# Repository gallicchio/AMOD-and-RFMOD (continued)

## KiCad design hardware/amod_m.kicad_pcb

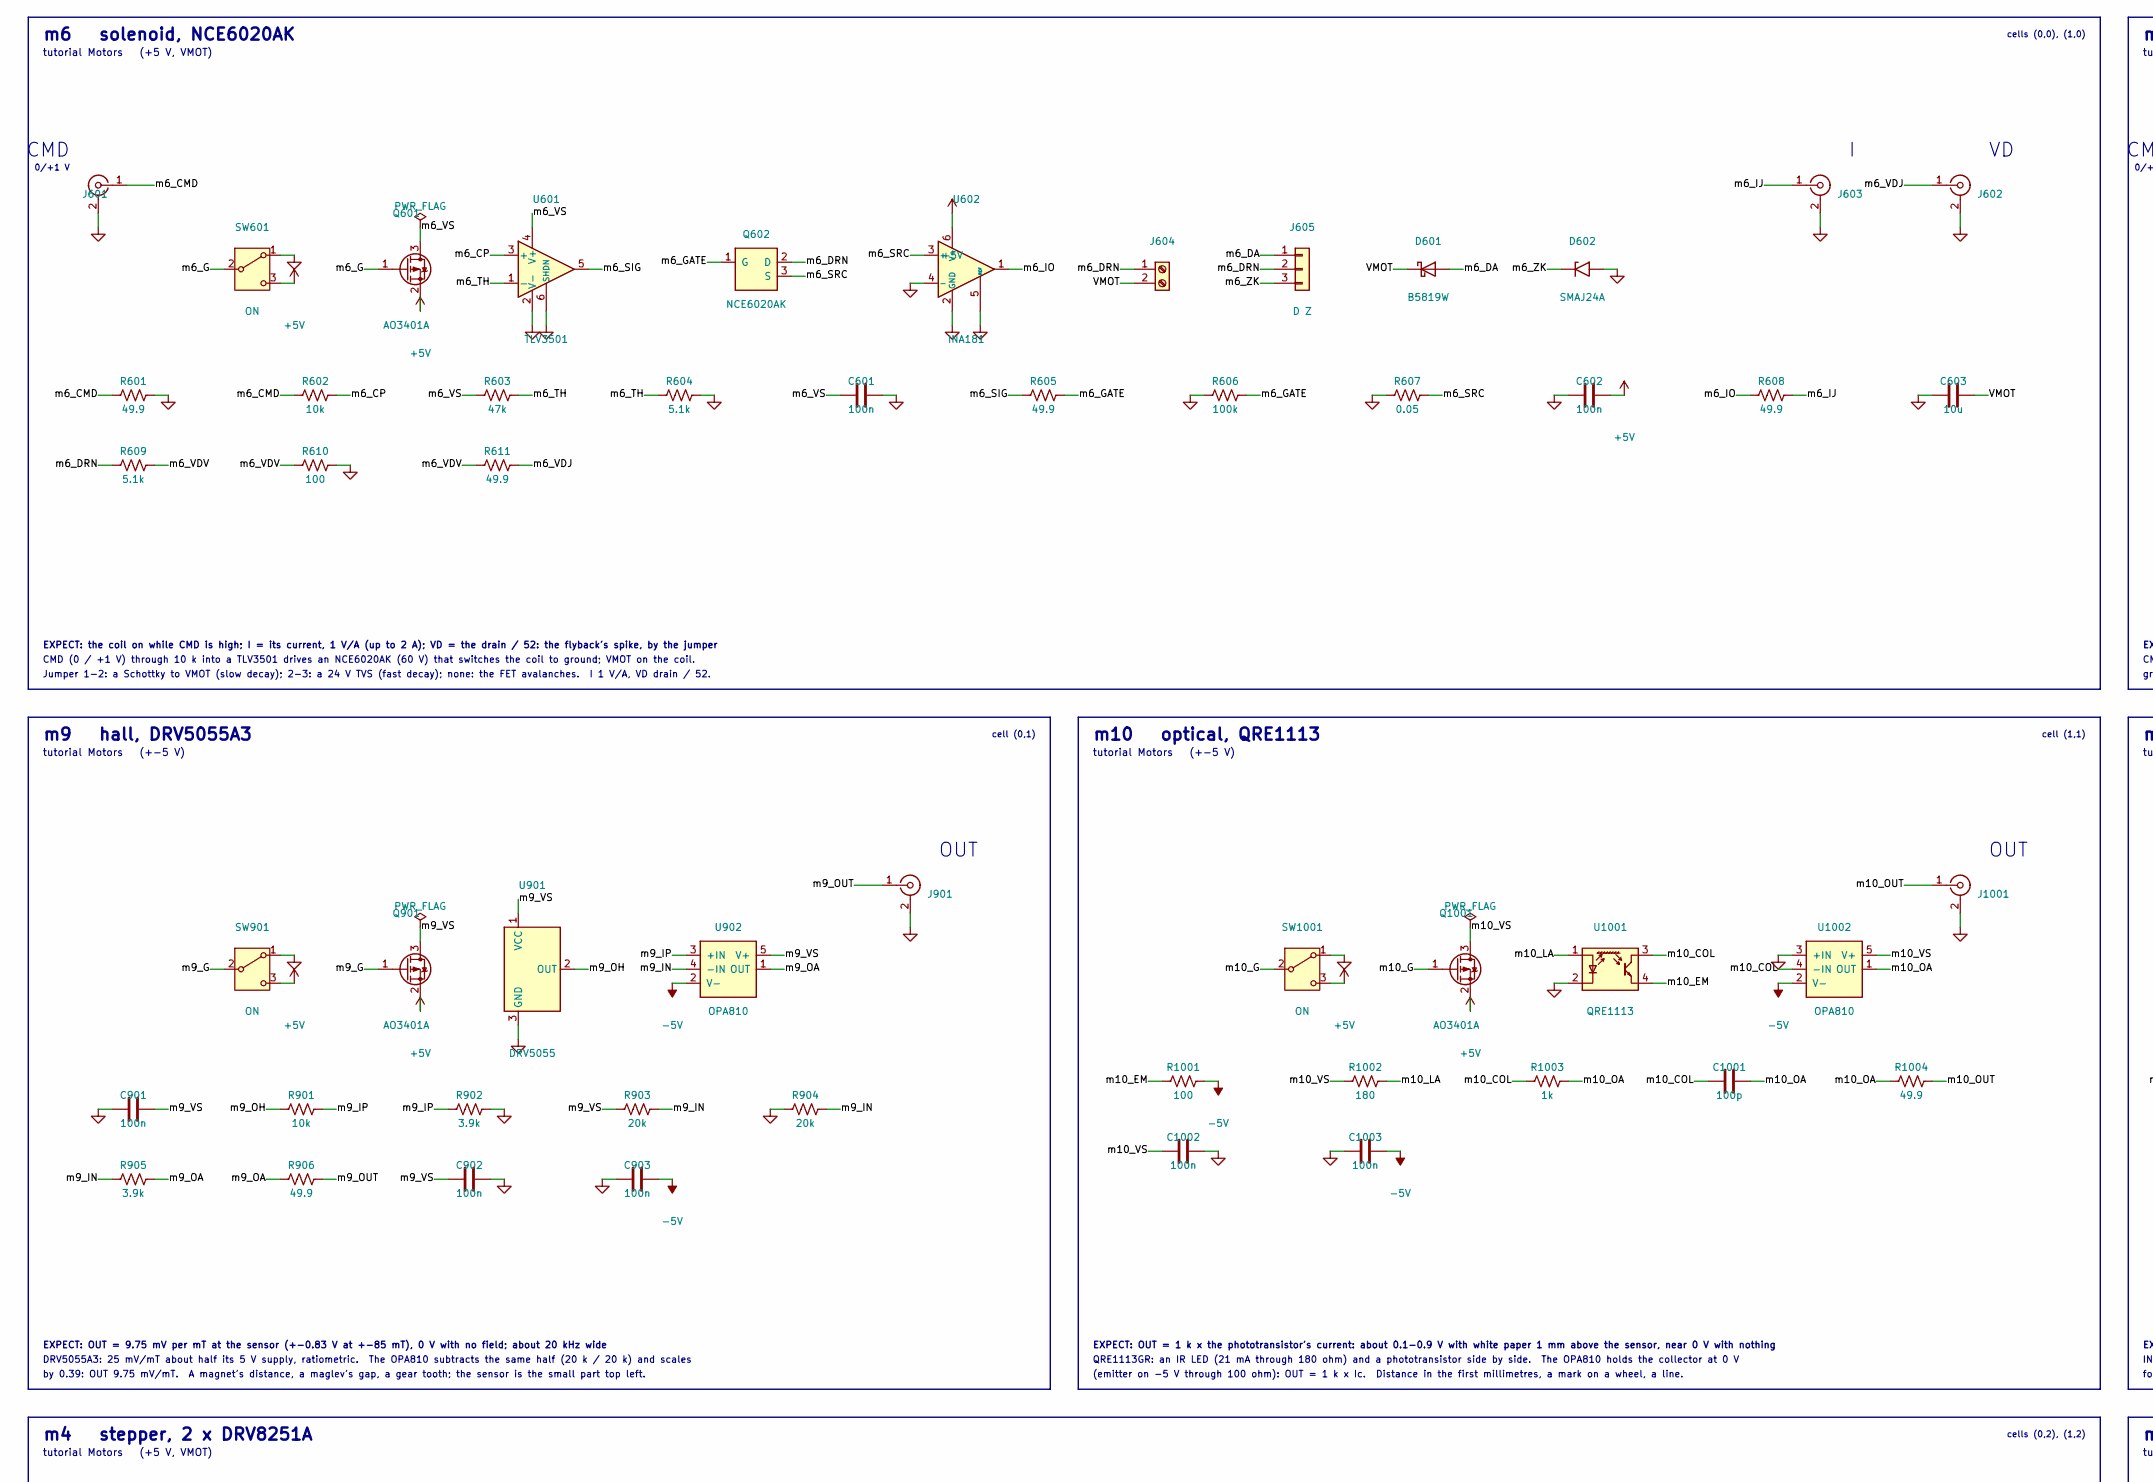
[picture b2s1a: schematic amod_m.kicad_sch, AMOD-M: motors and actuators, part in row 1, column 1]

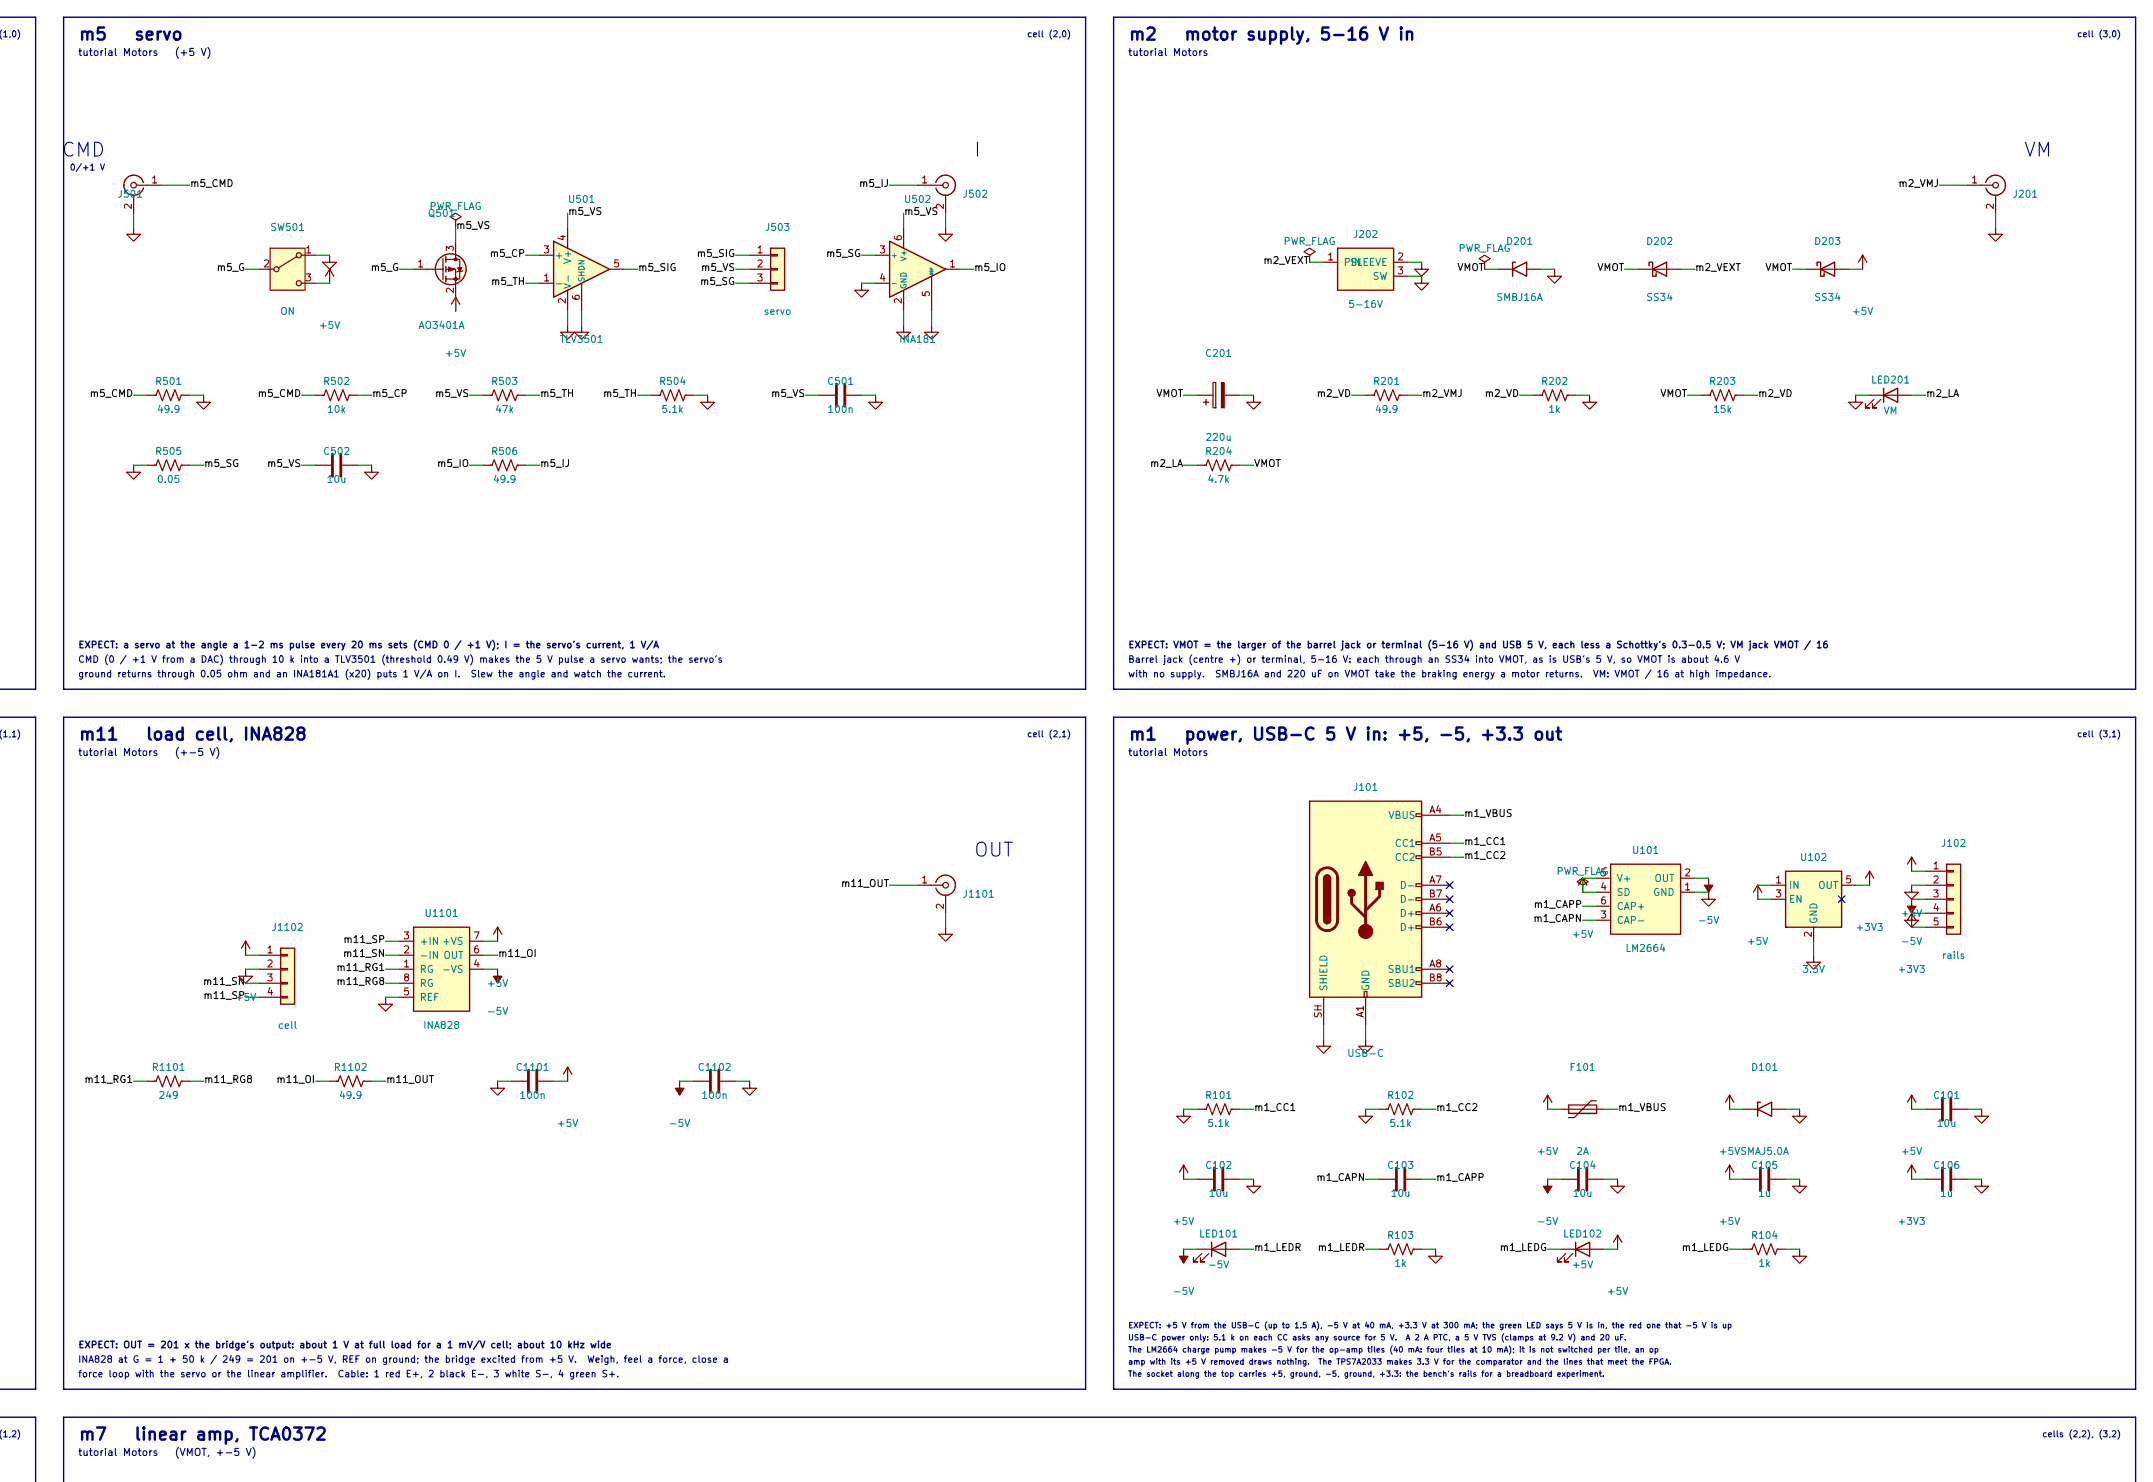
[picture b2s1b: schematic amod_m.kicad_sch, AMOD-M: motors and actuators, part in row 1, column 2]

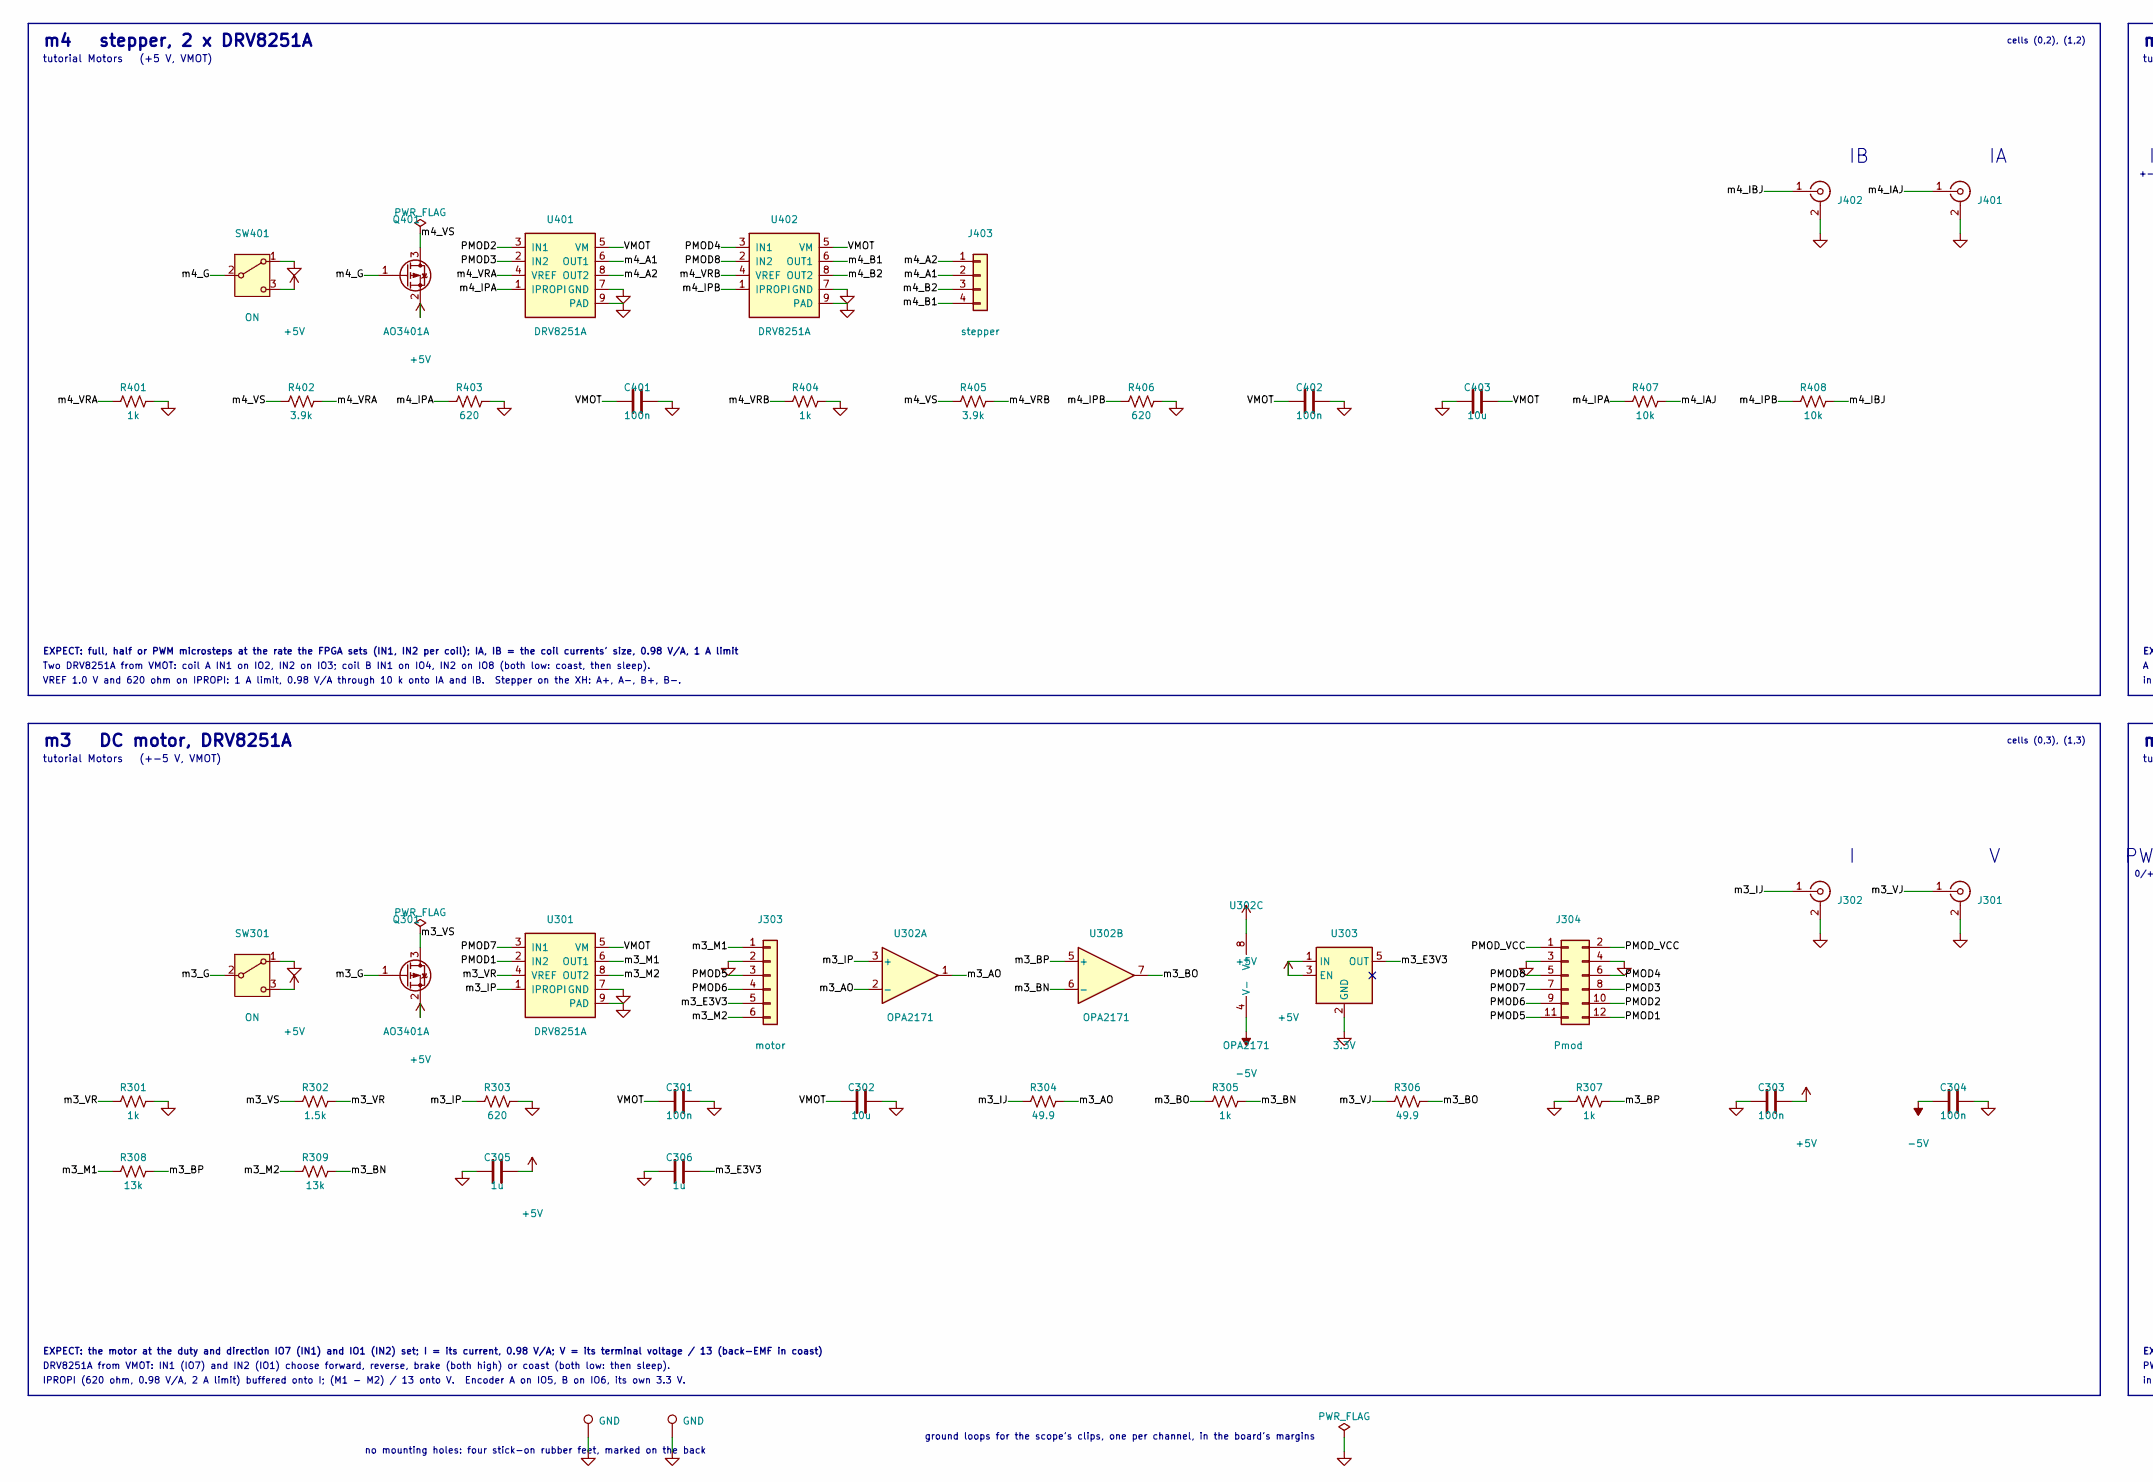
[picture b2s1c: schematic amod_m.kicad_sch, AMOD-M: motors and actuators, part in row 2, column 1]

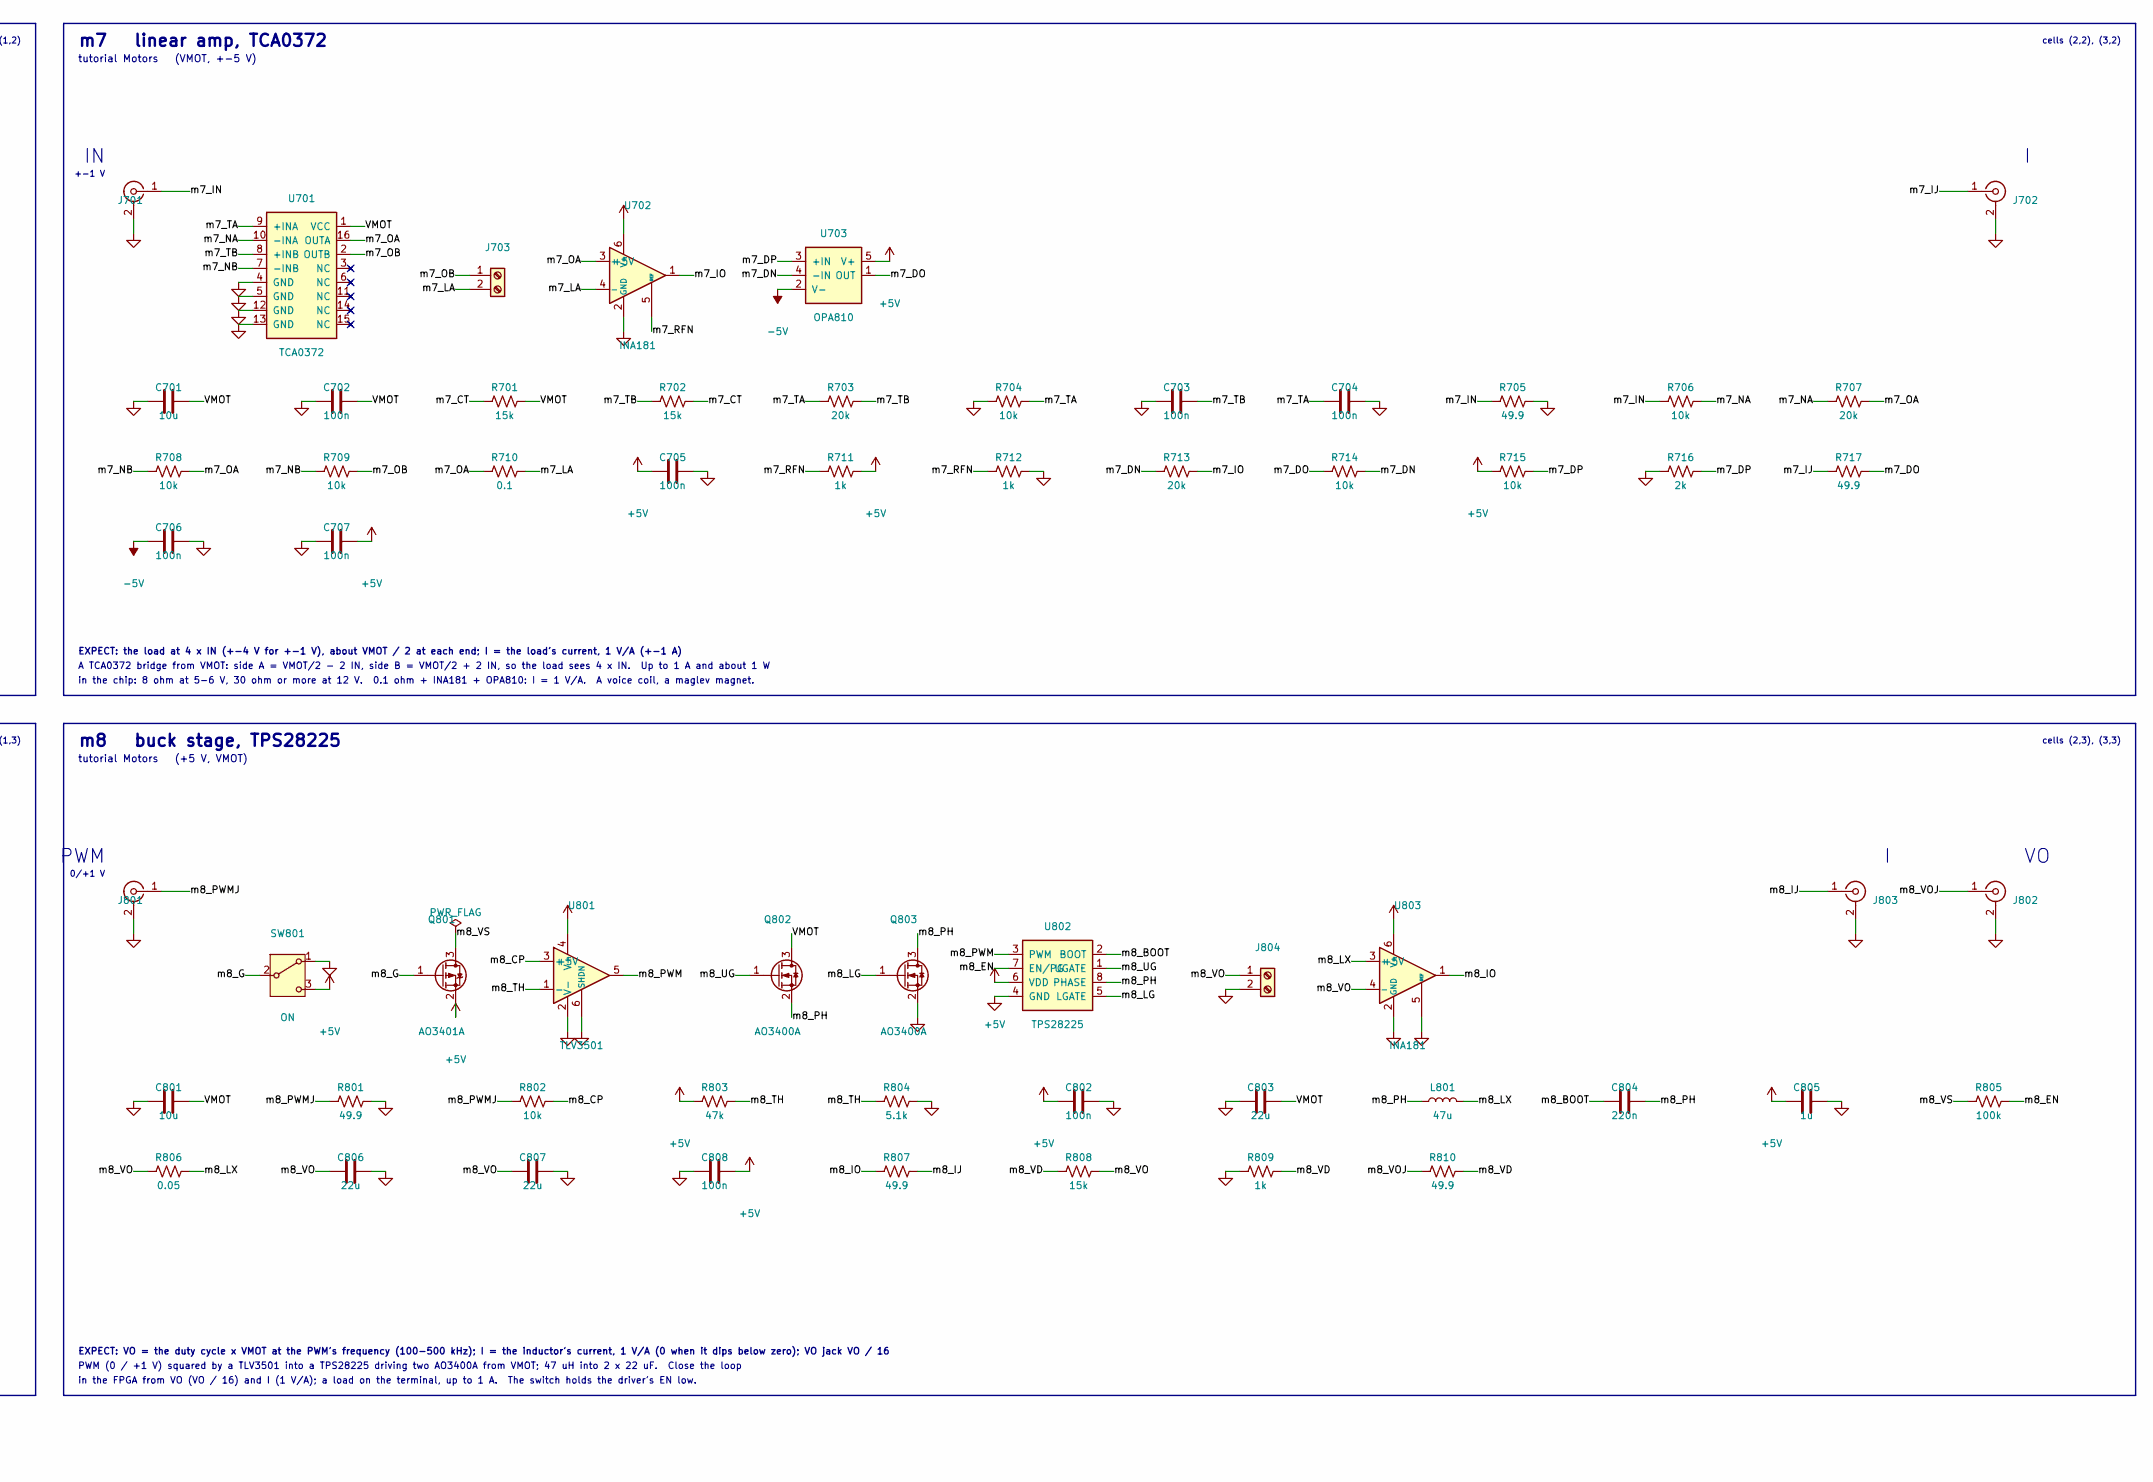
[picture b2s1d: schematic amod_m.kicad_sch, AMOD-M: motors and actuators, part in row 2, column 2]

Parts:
C101, C102, C103, C104, C302, C403, C502, C603, C701, C801: 10u; C_0805_2012Metric; MPN CL21A106KAYNNNE; LCSC C15850
C105, C106: 1u; C_0805_2012Metric; MPN CL21B105KBFNNNE; LCSC C28323
C201: 220u; CP_Elec_6.3x7.7; MPN XT220UF25V90RV0075; LCSC C2992606
C301, C303, C304, C401, C402, C501, C601, C602, C702, C703, C704, C705, C706, C707, C802, C808, C901, C902, C903, C1002, C1003, C1101, C1102: 100n; C_0402_1005Metric; MPN CL05B104KO5NNNC; LCSC C1525
C305, C306, C805: 1u; C_0603_1608Metric; MPN CL10A105KB8NNNC; LCSC C15849
C803, C806, C807: 22u; C_1206_3216Metric; MPN CL31A226KAHNNNE; LCSC C12891
C804: 220n; C_0402_1005Metric; MPN CL05B224KO5NNNC; LCSC C16772
C1001: 100p; C_0402_1005Metric; MPN 0402CG101J500NT; LCSC C1546
D101: SMAJ5.0A; D_SMA; MPN SMAJ5.0A; LCSC C78401
D201: SMBJ16A; D_SMB; MPN SMBJ16A; LCSC C353386
D202, D203: SS34; D_SMA; MPN SS34; LCSC C8678
D601: B5819W; D_SOD-123; MPN B5819W; LCSC C64885
D602: SMAJ24A; D_SMA; MPN SMAJ24A; LCSC C113962
F101: 2A; Fuse_1812_4532Metric; MPN MF-MSMF200-2; LCSC C210837
J101: USB-C; USB_C_Receptacle_HRO_TYPE-C-31-M-12; MPN TYPE-C-31-M-12; LCSC C165948
J102: rails; PinSocket_1x05_P2.54mm_Vertical; MPN PZ254-1-05-Z-8.5; LCSC C2894928
J201, J301, J302, J401, J402, J501, J502, J601, J602, J603, J701, J702, J801, J802, J803, J901, J1001, J1101: SMA; SMA_BWSMA-KE-Z001_Vertical; MPN BWSMA-KE-Z001; LCSC C496549
J202: 5-16V; BarrelJack_DC-005-5A_Horizontal; MPN DC-005-5A-2.0; LCSC C381116
J303: motor; JST_PH_B6B-PH-K_1x06_P2.00mm_Vertical; MPN B6B-PH-K-S(LF)(SN); LCSC C131342
J304: Pmod; PinHeader_2x06_P2.54mm_Horizontal_PZ254R-12-12P; MPN PZ254R-12-12P; LCSC C492434
J403: stepper; JST_XH_B4B-XH-A_1x04_P2.50mm_Vertical; MPN B4B-XH-A(LF)(SN); LCSC C144395
J503: servo; PinHeader_1x03_P2.54mm_Vertical; MPN PZ254V-11-03P; LCSC C2937625
J604: coil; TerminalBlock_KF301_1x02_P5.00mm; MPN KF301-5.0-2P; LCSC C474881
J605: D Z; PinHeader_1x03_P2.54mm_Vertical; MPN PZ254V-11-03P; LCSC C2937625
J703: load; TerminalBlock_KF301_1x02_P5.00mm; MPN KF301-5.0-2P; LCSC C474881
J804: out; TerminalBlock_KF301_1x02_P5.00mm; MPN KF301-5.0-2P; LCSC C474881
J1102: cell; JST_XH_B4B-XH-A_1x04_P2.50mm_Vertical; MPN B4B-XH-A(LF)(SN); LCSC C144395
L801: 47u; L_6x6_SWPA6045; MPN SWPA6045S470MT; LCSC C36414
LED101: -5V; LED_0805_2012Metric_Kbar; MPN NCD0805R1; LCSC C84256
LED102: +5V; LED_0805_2012Metric_Kbar; MPN KT-0805G; LCSC C2297
LED201: VM; LED_0805_2012Metric_Kbar; MPN KT-0805G; LCSC C2297
Q301, Q401, Q501, Q601, Q801, Q901, Q1001: AO3401A; SOT-23; MPN AO3401A; LCSC C15127
Q602: NCE6020AK; TO-252-2; MPN NCE6020AK; LCSC C108639
Q802, Q803: AO3400A; SOT-23; MPN AO3400A; LCSC C20917
R101, R102, R609: 5.1k; R_0805_2012Metric; MPN 0805W8F5101T5E; LCSC C27834
R103, R104: 1k; R_0805_2012Metric; MPN 0805W8F1001T5E; LCSC C17513
R201, R304, R306, R501, R506, R601, R605, R608, R611, R705, R717, R801, R807, R810, R906, R1004, R1102: 49.9; R_0402_1005Metric; MPN CRCW040249R9FKEDHP; LCSC C844112
R202, R301, R305, R307, R401, R404, R711, R712, R809, R1003: 1k; R_0402_1005Metric; MPN 0402WGF1001TCE; LCSC C11702
R203, R701, R702, R808: 15k; R_0402_1005Metric; MPN 0402WGF1502TCE; LCSC C25756
R204: 4.7k; R_0402_1005Metric; MPN 0402WGF4701TCE; LCSC C25900
R302: 1.5k; R_0402_1005Metric; MPN 0402WGF1501TCE; LCSC C25867
R303, R403, R406: 620; R_0402_1005Metric; MPN 0402WGF6200TCE; LCSC C4961
R308, R309: 13k; R_0402_1005Metric; MPN 0402WGF1302TCE; LCSC C25754
R402, R405, R902, R905: 3.9k; R_0402_1005Metric; MPN 0402WGF3901TCE; LCSC C51721
R407, R408, R502, R602, R704, R706, R708, R709, R714, R715, R802, R901: 10k; R_0402_1005Metric; MPN 0402WGF1002TCE; LCSC C25744
R503, R603, R803: 47k; R_0402_1005Metric; MPN 0402WGF4702TCE; LCSC C25792
R504, R604, R804: 5.1k; R_0402_1005Metric; MPN 0402WGF5101TCE; LCSC C25905
R505, R607, R806: 0.05; R_1206_3216Metric; MPN 1206W3F500MT5E; LCSC C127691
R606, R805: 100k; R_0402_1005Metric; MPN 0402WGF1003TCE; LCSC C25741
R610, R1001: 100; R_0402_1005Metric; MPN 0402WGF1000TCE; LCSC C25076
R703, R707, R713, R903, R904: 20k; R_0402_1005Metric; MPN 0402WGF2002TCE; LCSC C25765
R710: 0.1; R_1206_3216Metric; MPN 1206W4F100LT5E; LCSC C25334
R716: 2k; R_0402_1005Metric; MPN 0402WGF2001TCE; LCSC C4109
R1002: 180; R_0805_2012Metric; MPN 0805W8F1800T5E; LCSC C25270
R1101: 249; R_0402_1005Metric; MPN 0402WGF2490TCE; LCSC C25096
SW301, SW401, SW501, SW601, SW801, SW901, SW1001: ON; SW_SPDT_Shouhan_MSK12C02; MPN MSK12C02; LCSC C431540
TP9901, TP9902: GND; TestPoint_Loop_RH-5019; MPN RH-5019; LCSC C5199800
U101: LM2664; SOT-23-6; MPN LM2664M6X/NOPB; LCSC C108573
U102, U303: 3.3V; SOT-23-5; MPN TPS7A2033PDBVR; LCSC C2862740
U301, U401, U402: DRV8251A; HSOP-8-1EP_3.9x4.9mm_P1.27mm_EP2.41x3.1mm; MPN DRV8251ADDAR; LCSC C5218844
U302: OPA2171; SOIC-8_3.9x4.9mm_P1.27mm; MPN OPA2171AIDR; LCSC C40904
U501, U601, U801: TLV3501; SOT-23-6; MPN TLV3501AIDBVR; LCSC C193413
U502, U602, U702, U803: INA181; SOT-23-6; MPN INA181A1IDBVR; LCSC C2058943
U701: TCA0372; SOIC-16W_7.5x10.3mm_P1.27mm; MPN TCA0372DWR2G; LCSC C362060
U703, U902, U1002: OPA810; SOT-23-5; MPN OPA810IDBVR; LCSC C2833513
U802: TPS28225; SOIC-8_3.9x4.9mm_P1.27mm; MPN TPS28225DR; LCSC C52897
U901: DRV5055; SOT-23; MPN DRV5055A3QDBZR; LCSC C266128
U1001: QRE1113; OnSemi_CASE100CY; MPN QRE1113GR; LCSC C232862
U1101: INA828; SOIC-8_3.9x4.9mm_P1.27mm; MPN INA828IDR; LCSC C544342

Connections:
+3V3: C106.1, J102.5, U102.5 (OUT)
+5V: C101.1, C102.1, C105.1, C303.2, C305.2, C602.2, C705.1, C707.2, C802.1, C805.1, C808.2, C1101.2, D101.1 (A1), D203.2 (A), F101.1, J102.1, J1102.1, LED102.2 (A), Q301.2 (S), Q401.2 (S), Q501.2 (S), Q601.2 (S), Q801.2 (S), Q901.2 (S), Q1001.2 (S), R711.2, R715.1, R803.1, SW301.3 (C), SW401.3 (C), SW501.3 (C), SW601.3 (C), SW801.3 (C), SW901.3 (C), SW1001.3 (C), U101.4 (SD), U101.5 (V+), U102.1 (IN), U102.3 (EN), U302.8 (V+), U303.1 (IN), U303.3 (EN), U602.6 (V+), U702.6 (V+), U703.5 (V+), U801.4 (V+), U802.6 (VDD), U803.6 (V+), U1101.7 (+VS)
-5V: C104.1, C304.1, C706.1, C903.2, C1003.2, C1102.1, J102.3, LED101.1 (K), R1001.2, U101.2 (OUT), U302.4 (V-), U703.2 (V-), U902.2 (V-), U1002.2 (V-), U1101.4 (-VS)
/PMOD1: J304.12, U301.2 (IN2)
/PMOD2: J304.10, U401.3 (IN1)
/PMOD3: J304.8, U401.2 (IN2)
/PMOD4: J304.6, U402.3 (IN1)
/PMOD5: J303.3, J304.11
/PMOD6: J303.4, J304.9
/PMOD7: J304.7, U301.3 (IN1)
/PMOD8: J304.5, U402.2 (IN2)
/PMOD_VCC: J304.1, J304.2
/VMOT: C201.1, C301.1, C302.1, C401.1, C402.1, C403.2, C603.2, C701.2, C702.2, C801.2, C803.2, D201.1 (A1), D202.1 (K), D203.1 (K), D601.1 (K), J604.2, Q802.3 (D), R203.1, R204.2, R701.2, U301.5 (VM), U401.5 (VM), U402.5 (VM), U701.1 (VCC)
/m1_CAPN: C103.1, U101.3 (CAP-)
/m1_CAPP: C103.2, U101.6 (CAP+)
/m1_CC1: J101.A5 (CC1), R101.2
/m1_CC2: J101.B5 (CC2), R102.2
/m1_LEDG: LED102.1 (K), R104.1
/m1_LEDR: LED101.2 (A), R103.1
/m1_VBUS: F101.2, J101.A4 (VBUS), J101.A9 (VBUS), J101.B4 (VBUS), J101.B9 (VBUS)
/m2_LA: LED201.2 (A), R204.1
/m2_VD: R201.1, R202.1, R203.2
/m2_VEXT: D202.2 (A), J202.1 (PIN)
/m2_VMJ: J201.1 (In), R201.2
/m3_AO: R304.2, U302.1, U302.2 (-)
/m3_BN: R305.2, R309.2, U302.6 (-)
/m3_BO: R305.1, R306.2, U302.7
/m3_BP: R307.2, R308.2, U302.5 (+)
/m3_E3V3: C306.2, J303.5, U303.5 (OUT)
/m3_G: Q301.1 (G), SW301.2 (B)
/m3_IJ: J302.1 (In), R304.1
/m3_IP: R303.1, U301.1 (IPROPI), U302.3 (+)
/m3_M1: J303.1, R308.1, U301.6 (OUT1)
/m3_M2: J303.6, R309.1, U301.8 (OUT2)
/m3_VJ: J301.1 (In), R306.1
/m3_VR: R301.1, R302.2, U301.4 (VREF)
/m3_VS: Q301.3 (D), R302.1
/m4_A1: J403.2, U401.6 (OUT1)
/m4_A2: J403.1, U401.8 (OUT2)
/m4_B1: J403.4, U402.6 (OUT1)
/m4_B2: J403.3, U402.8 (OUT2)
/m4_G: Q401.1 (G), SW401.2 (B)
/m4_IAJ: J401.1 (In), R407.2
/m4_IBJ: J402.1 (In), R408.2
/m4_IPA: R403.1, R407.1, U401.1 (IPROPI)
/m4_IPB: R406.1, R408.1, U402.1 (IPROPI)
/m4_VRA: R401.1, R402.2, U401.4 (VREF)
/m4_VRB: R404.1, R405.2, U402.4 (VREF)
/m4_VS: Q401.3 (D), R402.1, R405.1
/m5_CMD: J501.1 (In), R501.1, R502.1
/m5_CP: R502.2, U501.3 (+)
/m5_G: Q501.1 (G), SW501.2 (B)
/m5_IJ: J502.1 (In), R506.2
/m5_IO: R506.1, U502.1
/m5_SG: J503.3, R505.2, U502.3 (+)
/m5_SIG: J503.1, U501.5
/m5_TH: R503.2, R504.1, U501.1 (-)
/m5_VS: C501.1, C502.1, J503.2, Q501.3 (D), R503.1, U501.4 (V+), U502.6 (V+)
/m6_CMD: J601.1 (In), R601.1, R602.1
/m6_CP: R602.2, U601.3 (+)
/m6_DA: D601.2 (A), J605.1
/m6_DRN: J604.1, J605.2, Q602.2 (D), R609.1
/m6_G: Q601.1 (G), SW601.2 (B)
/m6_GATE: Q602.1 (G), R605.2, R606.2
/m6_IJ: J603.1 (In), R608.2
/m6_IO: R608.1, U602.1
/m6_SIG: R605.1, U601.5
/m6_SRC: Q602.3 (S), R607.2, U602.3 (+)
/m6_TH: R603.2, R604.1, U601.1 (-)
/m6_VDJ: J602.1 (In), R611.2
/m6_VDV: R609.2, R610.1, R611.1
/m6_VS: C601.1, Q601.3 (D), R603.1, U601.4 (V+)
/m6_ZK: D602.1 (A1), J605.3
/m7_CT: R701.1, R702.2
/m7_DN: R713.1, R714.2, U703.4 (-IN)
/m7_DO: R714.1, R717.2, U703.1 (OUT)
/m7_DP: R715.2, R716.2, U703.3 (+IN)
/m7_IJ: J702.1 (In), R717.1
/m7_IN: J701.1 (In), R705.1, R706.1
/m7_IO: R713.2, U702.1
/m7_LA: J703.2, R710.2, U702.4 (-)
/m7_NA: R706.2, R707.1, U701.10 (-INA)
/m7_NB: R708.1, R709.1, U701.7 (-INB)
/m7_OA: R707.2, R708.2, R710.1, U701.16 (OUTA), U702.3 (+)
/m7_OB: J703.1, R709.2, U701.2 (OUTB)
/m7_RFN: R711.1, R712.1, U702.5 (REF)
/m7_TA: C704.1, R703.1, R704.2, U701.9 (+INA)
/m7_TB: C703.2, R702.1, R703.2, U701.8 (+INB)
/m8_BOOT: C804.1, U802.2 (BOOT)
/m8_CP: R802.2, U801.3 (+)
/m8_EN: R805.2, U802.7 (EN/PG)
/m8_G: Q801.1 (G), SW801.2 (B)
/m8_IJ: J803.1 (In), R807.2
/m8_IO: R807.1, U803.1
/m8_LG: Q803.1 (G), U802.5 (LGATE)
/m8_LX: L801.2, R806.2, U803.3 (+)
/m8_PH: C804.2, L801.1, Q802.2 (S), Q803.3 (D), U802.8 (PHASE)
/m8_PWM: U801.5, U802.3 (PWM)
/m8_PWMJ: J801.1 (In), R801.1, R802.1
/m8_TH: R803.2, R804.1, U801.1 (-)
/m8_UG: Q802.1 (G), U802.1 (UGATE)
/m8_VD: R808.1, R809.2, R810.2
/m8_VO: C806.1, C807.1, J804.1, R806.1, R808.2, U803.4 (-)
/m8_VOJ: J802.1 (In), R810.1
/m8_VS: Q801.3 (D), R805.1
/m9_G: Q901.1 (G), SW901.2 (B)
/m9_IN: R903.2, R904.2, R905.1, U902.4 (-IN)
/m9_IP: R901.2, R902.1, U902.3 (+IN)
/m9_OA: R905.2, R906.1, U902.1 (OUT)
/m9_OH: R901.1, U901.2 (OUT)
/m9_OUT: J901.1 (In), R906.2
/m9_VS: C901.2, C902.1, Q901.3 (D), R903.1, U901.1 (VCC), U902.5 (V+)
/m10_COL: C1001.1, R1003.1, U1001.3, U1002.4 (-IN)
/m10_EM: R1001.1, U1001.4
/m10_G: Q1001.1 (G), SW1001.2 (B)
/m10_LA: R1002.2, U1001.1 (A)
/m10_OA: C1001.2, R1003.2, R1004.1, U1002.1 (OUT)
/m10_OUT: J1001.1 (In), R1004.2
/m10_VS: C1002.1, Q1001.3 (D), R1002.1, U1002.5 (V+)
/m11_OI: R1102.1, U1101.6 (OUT)
/m11_OUT: J1101.1 (In), R1102.2
/m11_RG1: R1101.1, U1101.1 (RG)
/m11_RG8: R1101.2, U1101.8 (RG)
/m11_SN: J1102.3, U1101.2 (-IN)
/m11_SP: J1102.4, U1101.3 (+IN)
GND: C101.2, C102.2, C104.2, C105.2, C106.2, C201.2, C301.2, C302.2, C303.1, C304.2, C305.1, C306.1, C401.2, C402.2, C403.1, C501.2, C502.2, C601.2, C602.1, C603.1, C701.1, C702.1, C703.1, C704.2, C705.2, C706.2, C707.1, C801.1, C802.2, C803.1, C805.2, C806.2, C807.2, C808.1, C901.1, C902.2, C903.1, C1002.2, C1003.1, C1101.1, C1102.2, D101.2 (A2), D201.2 (A2), D602.2 (A2), J101.A1 (GND), J101.A12 (GND), J101.B1 (GND), J101.B12 (GND), J101.SH (SHIELD), J102.2, J102.4, J201.2 (Ext), J202.2 (SLEEVE), J202.3 (SW), J301.2 (Ext), J302.2 (Ext), J303.2, J304.3, J304.4, J401.2 (Ext), J402.2 (Ext), J501.2 (Ext), J502.2 (Ext), J601.2 (Ext), J602.2 (Ext), J603.2 (Ext), J701.2 (Ext), J702.2 (Ext), J801.2 (Ext), J802.2 (Ext), J803.2 (Ext), J804.2, J901.2 (Ext), J1001.2 (Ext), J1101.2 (Ext), J1102.2, LED201.1 (K), Q803.2 (S), R101.1, R102.1, R103.2, R104.2, R202.2, R301.2, R303.2, R307.1, R401.2, R403.2, R404.2, R406.2, R501.2, R504.2, R505.1, R601.2, R604.2, R606.1, R607.1, R610.2, R704.1, R705.2, R712.2, R716.1, R801.2, R804.2, R809.1, R902.2, R904.1, SW301.1 (A), SW401.1 (A), SW501.1 (A), SW601.1 (A), SW801.1 (A), SW901.1 (A), SW1001.1 (A), TP9901.1, TP9902.1, U101.1 (GND), U102.2 (GND), U301.7 (GND), U301.9 (PAD), U303.2 (GND), U401.7 (GND), U401.9 (PAD), U402.7 (GND), U402.9 (PAD), U501.2 (V-), U501.6 (SHDN), U502.2 (GND), U502.4 (-), U502.5 (REF), U601.2 (V-), U601.6 (SHDN), U602.2 (GND), U602.4 (-), U602.5 (REF), U701.4 (GND), U701.5 (GND), U701.12 (GND), U701.13 (GND), U702.2 (GND), U801.2 (V-), U801.6 (SHDN), U802.4 (GND), U803.2 (GND), U803.5 (REF), U901.3 (GND), U1001.2 (K), U1002.3 (+IN), U1101.5 (REF)

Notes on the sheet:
CMD
OUT
cells (2,2), (3,2)
cell (2,1)
Two DRV8251A from VMOT: coil A IN1 on IO2, IN2 on IO3; coil B IN1 on IO4, IN2 on IO8 (both low: coast, then sleep).
DRV8251A from VMOT: IN1 (IO7) and IN2 (IO1) choose forward, reverse, brake (both high) or coast (both low: then sleep).
cell (2,0)
m4 stepper, 2 x DRV8251A
INA828 at G = 1 + 50 k / 249 = 201 on +-5 V, REF on ground; the bridge excited from +5 V. Weigh, feel a force, close a
USB-C power only: 5.1 k on each CC asks any source for 5 V. A 2 A PTC, a 5 V TVS (clamps at 9.2 V) and 20 uF.
EXPECT: the coil on while CMD is high; I = its current, 1 V/A (up to 2 A); VD = the drain / 52: the flyback's spike, by the jumper
EXPECT: VO = the duty cycle x VMOT at the PWM's frequency (100-500 kHz); I = the inductor's current, 1 V/A (0 when it dips below zero); VO jack VO / 16
The socket along the top carries +5, ground, -5, ground, +3.3: the bench's rails for a breadboard experiment.
in the FPGA from VO (VO / 16) and I (1 V/A); a load on the terminal, up to 1 A. The switch holds the driver's EN low.
cell (0,1)
m3 DC motor, DRV8251A
tutorial Motors
cells (0,0), (1,0)
A TCA0372 bridge from VMOT: side A = VMOT/2 - 2 IN, side B = VMOT/2 + 2 IN, so the load sees 4 x IN. Up to 1 A and about 1 W
cells (2,3), (3,3)
amp with its +5 V removed draws nothing. The TPS7A2033 makes 3.3 V for the comparator and the lines that meet the FPGA.
PWM
EXPECT: the load at 4 x IN (+-4 V for +-1 V), about VMOT / 2 at each end; I = the load's current, 1 V/A (+-1 A)
0/+1 V
The LM2664 charge pump makes -5 V for the op-amp tiles (40 mA: four tiles at 10 mA); it is not switched per tile, an op
tutorial Motors (+5 V, VMOT)
VREF 1.0 V and 620 ohm on IPROPI: 1 A limit, 0.98 V/A through 10 k onto IA and IB. Stepper on the XH: A+, A-, B+, B-.
tutorial Motors (+-5 V, VMOT)
cells (0,3), (1,3)
ground loops for the scope's clips, one per channel, in the board's margins
Barrel jack (centre +) or terminal, 5-16 V: each through an SS34 into VMOT, as is USB's 5 V, so VMOT is about 4.6 V
m11 load cell, INA828
+-1 V
tutorial Motors (+-5 V)
CMD (0 / +1 V from a DAC) through 10 k into a TLV3501 (threshold 0.49 V) makes the 5 V pulse a servo wants; the servo's
no mounting holes: four stick-on rubber feet, marked on the back
CMD (0 / +1 V) through 10 k into a TLV3501 drives an NCE6020AK (60 V) that switches the coil to ground; VMOT on the coil.
in the chip: 8 ohm at 5-6 V, 30 ohm or more at 12 V. 0.1 ohm + INA181 + OPA810: I = 1 V/A. A voice coil, a maglev magnet.
m5 servo
EXPECT: VMOT = the larger of the barrel jack or terminal (5-16 V) and USB 5 V, each less a Schottky's 0.3-0.5 V; VM jack VMOT / 16
